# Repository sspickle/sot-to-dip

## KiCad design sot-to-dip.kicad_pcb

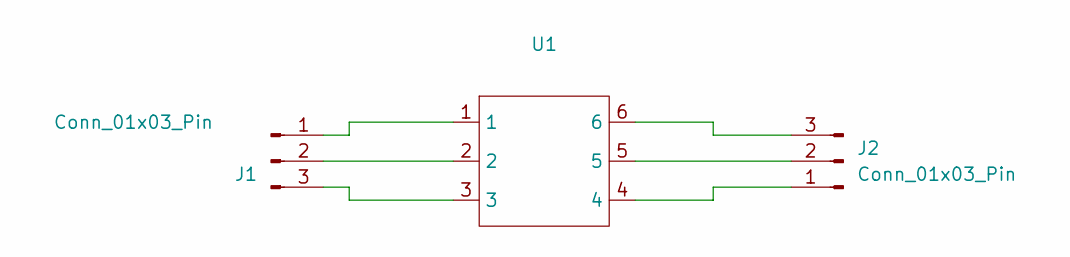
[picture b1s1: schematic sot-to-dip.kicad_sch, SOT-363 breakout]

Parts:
J1, J2: Conn_01x03_Pin; PinHeader_1x03_P2.54mm_Vertical
U1: SOT-363_SC-70-6_Handsoldering

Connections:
unnamed: J1.1, U1.1
unnamed: J1.2, U1.2
unnamed: J1.3, U1.3
unnamed: J2.1, U1.4
unnamed: J2.2, U1.5
unnamed: J2.3, U1.6

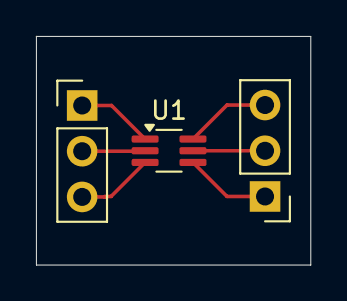
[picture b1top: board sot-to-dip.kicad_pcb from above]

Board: 2 copper layers, 15.2 x 12.7 mm, 3 parts (0 on the bottom side), 6 nets.

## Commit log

2025-11-20 add readme
2025-11-22 add freecad drawing
